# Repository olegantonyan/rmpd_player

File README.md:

rmpd_player

ESP32
VS1011
micro sd

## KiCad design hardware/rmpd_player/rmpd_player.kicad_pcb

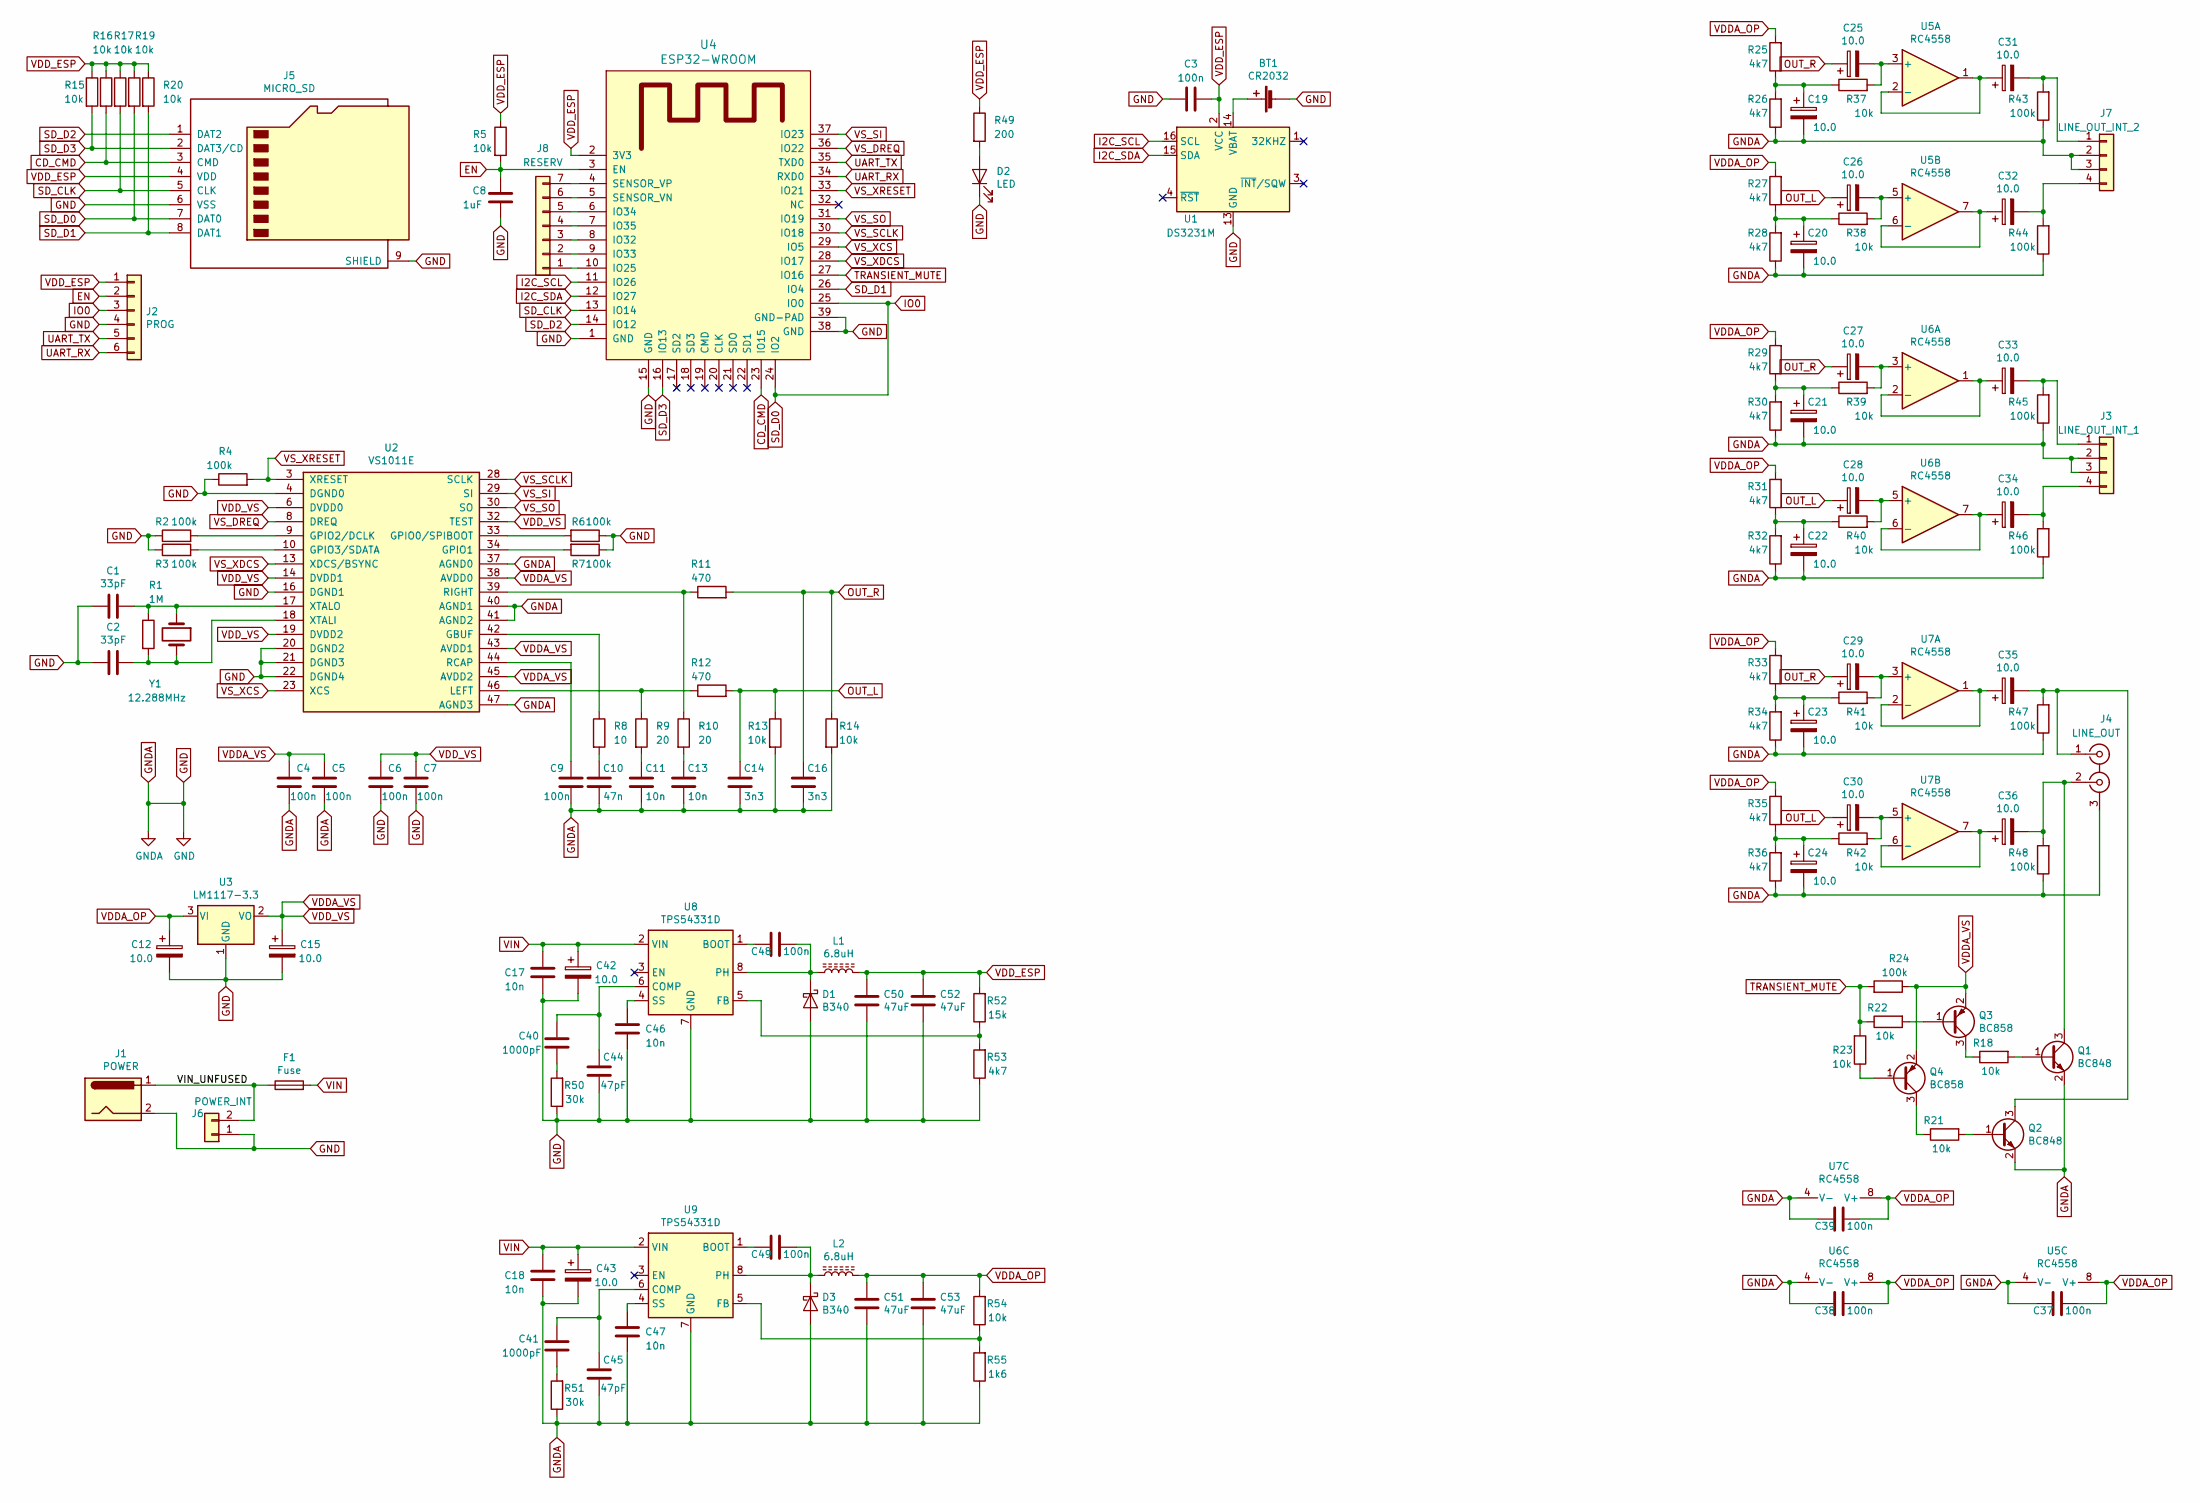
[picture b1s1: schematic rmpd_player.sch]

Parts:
BT1: CR2032; Keystone_103_1x20mm-CoinCell
C1, C2: 33pF; C_0805
C3, C4, C5, C6, C7, C9, C37, C38, C39, C48, C49: 100n; C_0805
C8: 1uF; C_0805
C10: 47n; C_0805
C11, C13, C17, C18, C46, C47: 10n; C_0805
C12, C15, C19, C20, C21, C22, C23, C24, C25, C26, C27, C28, C29, C30, C31, C32, C33, C34, C35, C36, C42, C43: 10.0; CP_Radial_D5.0mm_P2.50mm
C14, C16: 3n3; C_0805
C40, C41: 1000pF; C_0805
C44, C45: 47pF; C_0805
C50, C51, C52, C53: 47uF; C_1206
D1, D3: B340; PhotoDiode_SMD-DIL2_4.5x4
D2: LED; LED_D3.0mm
F1: Fuse; Fuse_SMD1206_Reflow
J1: POWER; BARREL_JACK
J2: PROG; Pin_Header_Straight_1x06_Pitch2.54mm
J3: LINE_OUT_INT_1; Pin_Header_Straight_1x04_Pitch2.54mm
J4: LINE_OUT; 2RCA
J5: MICRO_SD; Conn_uSDcard
J6: POWER_INT; Pin_Header_Straight_1x02_Pitch2.54mm
J7: LINE_OUT_INT_2; Pin_Header_Straight_1x04_Pitch2.54mm
J8: RESERV; Pin_Header_Straight_1x07_Pitch2.54mm
L1, L2: 6.8uH; L_6.3x6.3_H3
Q1, Q2: BC848; SOT-23
Q3, Q4: BC858; SOT-23
R1: 1M; R_0805
R2, R3, R4, R6, R7, R24, R43, R44, R45, R46, R47, R48: 100k; R_0805
R5, R13, R14, R15, R16, R17, R18, R19, R20, R21, R22, R23, R37, R38, R39, R40, R41, R42, R54: 10k; R_0805
R8: 10; R_0805
R9, R10: 20; R_0805
R11, R12: 470; R_0805
R25, R26, R27, R28, R29, R30, R31, R32, R33, R34, R35, R36, R53: 4k7; R_0805
R49: 200; R_0805
R50, R51: 30k; R_0805
R52: 15k; R_0805
R55: 1k6; R_0805
U1: DS3231M; SOIC-16W_7.5x10.3mm_Pitch1.27mm
U2: VS1011E; LQFP-48_7x7mm_Pitch0.5mm
U3: LM1117-3.3; SOT-223
U4: ESP32-WROOM
U5, U6, U7: RC4558; SO-8
U8, U9: TPS54331D; SOIC-8_3.9x4.9mm_Pitch1.27mm
Y1: 12.288MHz; Crystal_HC18-U_Vertical

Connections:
/VIN_UNFUSED: F1.1, J1.1, J6.2
CD_CMD: J5.3 (CMD), R16.2, U4.23 (IO15)
EN: C8.2, J2.2, R5.2, U4.3 (EN)
GND: BT1.2 (-), C1.2, C2.2, C3.1, C4.2, C5.2, C6.2, C7.2, C8.1, C9.2, C10.1, C11.1, C12.2, C13.1, C14.1, C15.2, C16.1, C17.2, C18.2, C19.2, C20.2, C21.2, C22.2, C23.2, C24.2, C37.2, C38.2, C39.2, C42.2, C43.2, C44.2, C45.2, C46.2, C47.2, C50.2, C51.2, C52.2, C53.2, D1.2 (A), D2.1 (K), D3.2 (A), J1.2, J2.4, J3.2, J3.3, J4.3 (EXT), J5.6 (VSS), J5.9 (SHIELD), J6.1, J7.2, J7.3, Q1.2 (E), Q2.2 (E), R2.1, R3.1, R4.1, R6.1, R7.1, R13.2, R14.2, R26.1, R28.1, R30.1, R32.1, R34.1, R36.1, R43.1, R44.1, R45.1, R46.1, R47.1, R48.1, R50.1, R51.1, R53.1, R55.1, U1.5 (GND), U1.6 (GND), U1.7 (GND), U1.8 (GND), U1.9 (GND), U1.10 (GND), U1.11 (GND), U1.12 (GND), U1.13 (GND), U2.4 (DGND0), U2.16 (DGND1), U2.20 (DGND2), U2.21 (DGND3), U2.22 (DGND4), U2.37 (AGND0), U2.40 (AGND1), U2.41 (AGND2), U2.47 (AGND3), U3.1 (GND), U4.1 (GND), U4.15 (GND), U4.38 (GND), U4.39 (GND-PAD), U5.4 (V-), U6.4 (V-), U7.4 (V-), U8.7 (GND), U9.7 (GND)
I2C_SCL: U1.16 (SCL), U4.11 (IO26)
I2C_SDA: U1.15 (SDA), U4.12 (IO27)
IO0: J2.3, J5.7 (DAT0), R19.2, U4.24 (IO2), U4.25 (IO0)
unnamed: BT1.1 (+), U1.14 (VBAT)
unnamed: C1.1, R1.1, U2.17 (XTALO), Y1.1
unnamed: C2.1, R1.2, U2.18 (XTALI), Y1.2
unnamed: C9.1, U2.44 (RCAP)
unnamed: C10.2, R8.2
unnamed: C11.2, R9.2
unnamed: C13.2, R10.2
unnamed: C19.1, R25.1, R26.2, R37.1
unnamed: C20.1, R27.1, R28.2, R38.1
unnamed: C21.1, R29.1, R30.2, R39.1
unnamed: C22.1, R31.1, R32.2, R40.1
unnamed: C23.1, R33.1, R34.2, R41.1
unnamed: C24.1, R35.1, R36.2, R42.1
unnamed: C25.2, R37.2, U5.3 (+)
unnamed: C26.2, R38.2, U5.5 (+)
unnamed: C27.2, R39.2, U6.3 (+)
unnamed: C28.2, R40.2, U6.5 (+)
unnamed: C29.2, R41.2, U7.3 (+)
unnamed: C30.2, R42.2, U7.5 (+)
unnamed: C31.1, U5.1, U5.2 (-)
unnamed: C31.2, J7.1, R43.2
unnamed: C32.1, U5.6 (-), U5.7
unnamed: C32.2, J7.4, R44.2
unnamed: C33.1, U6.1, U6.2 (-)
unnamed: C33.2, J3.1, R45.2
unnamed: C34.1, U6.6 (-), U6.7
unnamed: C34.2, J3.4, R46.2
unnamed: C35.1, U7.1, U7.2 (-)
unnamed: C35.2, J4.1 (IN1), Q2.3 (C), R47.2
unnamed: C36.1, U7.6 (-), U7.7
unnamed: C36.2, J4.2 (IN2), Q1.3 (C), R48.2
unnamed: C40.1, C44.1, U8.6 (COMP)
unnamed: C40.2, R50.2
unnamed: C41.1, C45.1, U9.6 (COMP)
unnamed: C41.2, R51.2
unnamed: C46.1, U8.4 (SS)
unnamed: C47.1, U9.4 (SS)
unnamed: C48.1, D1.1 (K), L1.1, U8.8 (PH)
unnamed: C48.2, U8.1 (BOOT)
unnamed: C49.1, D3.1 (K), L2.1, U9.8 (PH)
unnamed: C49.2, U9.1 (BOOT)
unnamed: D2.2 (A), R49.2
unnamed: J8.1, U4.10 (IO25)
unnamed: J8.2, U4.9 (IO33)
unnamed: J8.3, U4.8 (IO32)
unnamed: J8.4, U4.7 (IO35)
unnamed: J8.5, U4.6 (IO34)
unnamed: J8.6, U4.5 (SENSOR_VN)
unnamed: J8.7, U4.4 (SENSOR_VP)
unnamed: Q1.1 (B), R18.2
unnamed: Q2.1 (B), R21.2
unnamed: Q3.1 (B), R22.2
unnamed: Q3.3 (C), R18.1
unnamed: Q4.1 (B), R23.1
unnamed: Q4.3 (C), R21.1
unnamed: R2.2, U2.9 (GPIO2/DCLK)
unnamed: R3.2, U2.10 (GPIO3/SDATA)
unnamed: R6.2, U2.33 (GPIO0/SPIBOOT)
unnamed: R7.2, U2.34 (GPIO1)
unnamed: R8.1, U2.42 (GBUF)
unnamed: R10.1, R11.1, U2.39 (RIGHT)
unnamed: R9.1, R12.1, U2.46 (LEFT)
unnamed: R52.1, R53.2, U8.5 (FB)
unnamed: R54.1, R55.2, U9.5 (FB)
OUT_L: C14.2, C26.1, C28.1, C30.1, R12.2, R13.1
OUT_R: C16.2, C25.1, C27.1, C29.1, R11.2, R14.1
SD_CLK: J5.5 (CLK), R17.2, U4.13 (IO14)
SD_D1: J5.8 (DAT1), R20.2, U4.26 (IO4)
SD_D2: J5.1 (DAT2), U4.14 (IO12)
SD_D3: J5.2 (DAT3/CD), R15.2, U4.16 (IO13)
TRANSIENT_MUTE: R22.1, R23.2, R24.2, U4.27 (IO16)
UART_RX: J2.6, U4.34 (RXD0)
UART_TX: J2.5, U4.35 (TXD0)
VDDA_OP: C12.1, C37.1, C38.1, C39.1, C51.1, C53.1, L2.2, R25.2, R27.2, R29.2, R31.2, R33.2, R35.2, R54.2, U3.3 (VI), U5.8 (V+), U6.8 (V+), U7.8 (V+)
VDDA_VS: C4.1, C5.1, C6.1, C7.1, C15.1, Q3.2 (E), Q4.2 (E), R24.1, U2.6 (DVDD0), U2.14 (DVDD1), U2.19 (DVDD2), U2.32 (TEST), U2.38 (AVDD0), U2.43 (AVDD1), U2.45 (AVDD2), U3.2 (VO)
VDD_ESP: C3.2, C50.1, C52.1, J2.1, J5.4 (VDD), L1.2, R5.1, R15.1, R16.1, R17.1, R19.1, R20.1, R49.1, R52.2, U1.2 (VCC), U4.2 (3V3)
VIN: C17.1, C18.1, C42.1, C43.1, F1.2, U8.2 (VIN), U9.2 (VIN)
VS_DREQ: U2.8 (DREQ), U4.36 (IO22)
VS_SCLK: U2.28 (SCLK), U4.30 (IO18)
VS_SI: U2.29 (SI), U4.37 (IO23)
VS_SO: U2.30 (SO), U4.31 (IO19)
VS_XCS: U2.23 (XCS), U4.29 (IO5)
VS_XDCS: U2.13 (XDCS/BSYNC), U4.28 (IO17)
VS_XRESET: R4.2, U2.3 (XRESET), U4.33 (IO21)

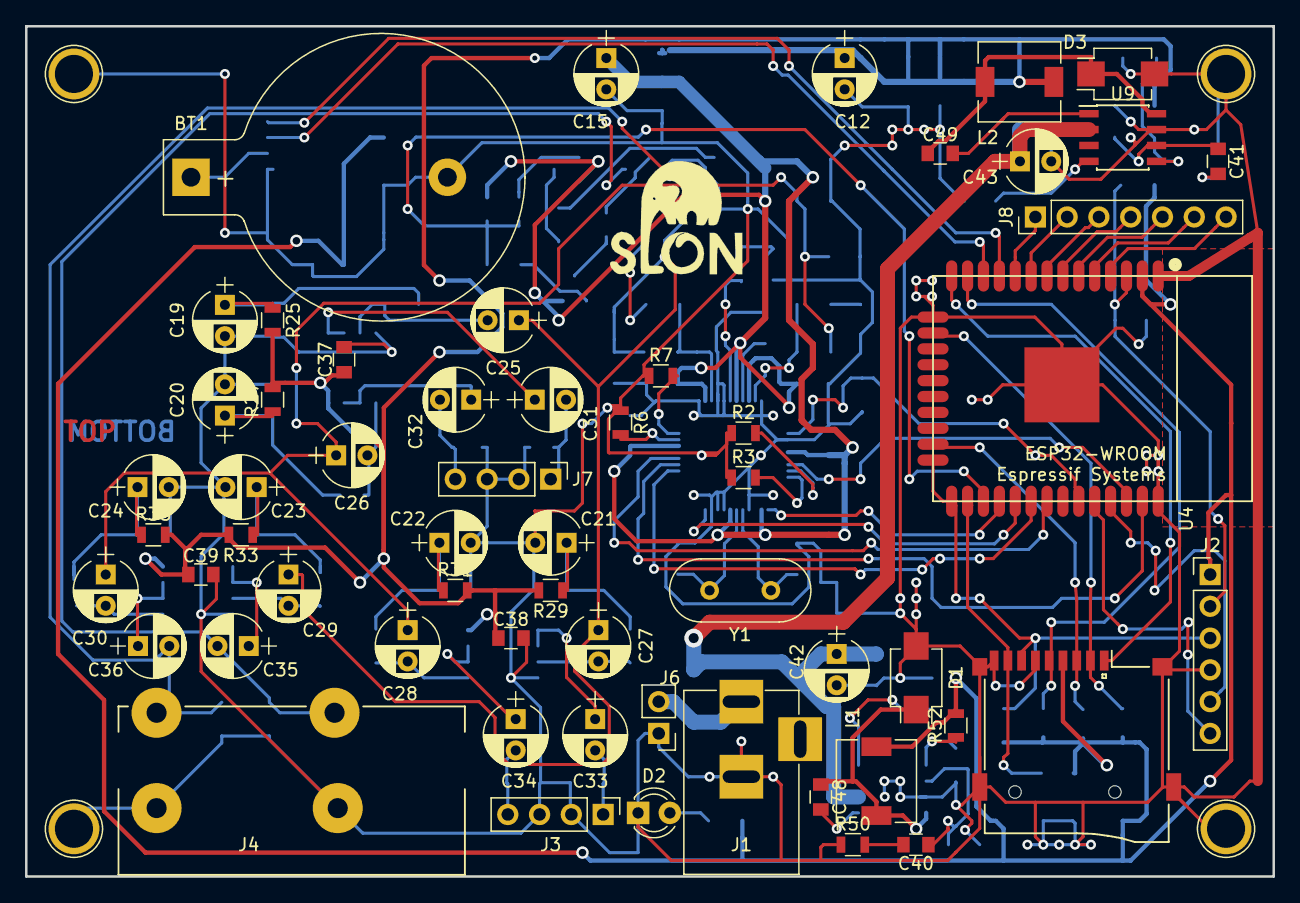
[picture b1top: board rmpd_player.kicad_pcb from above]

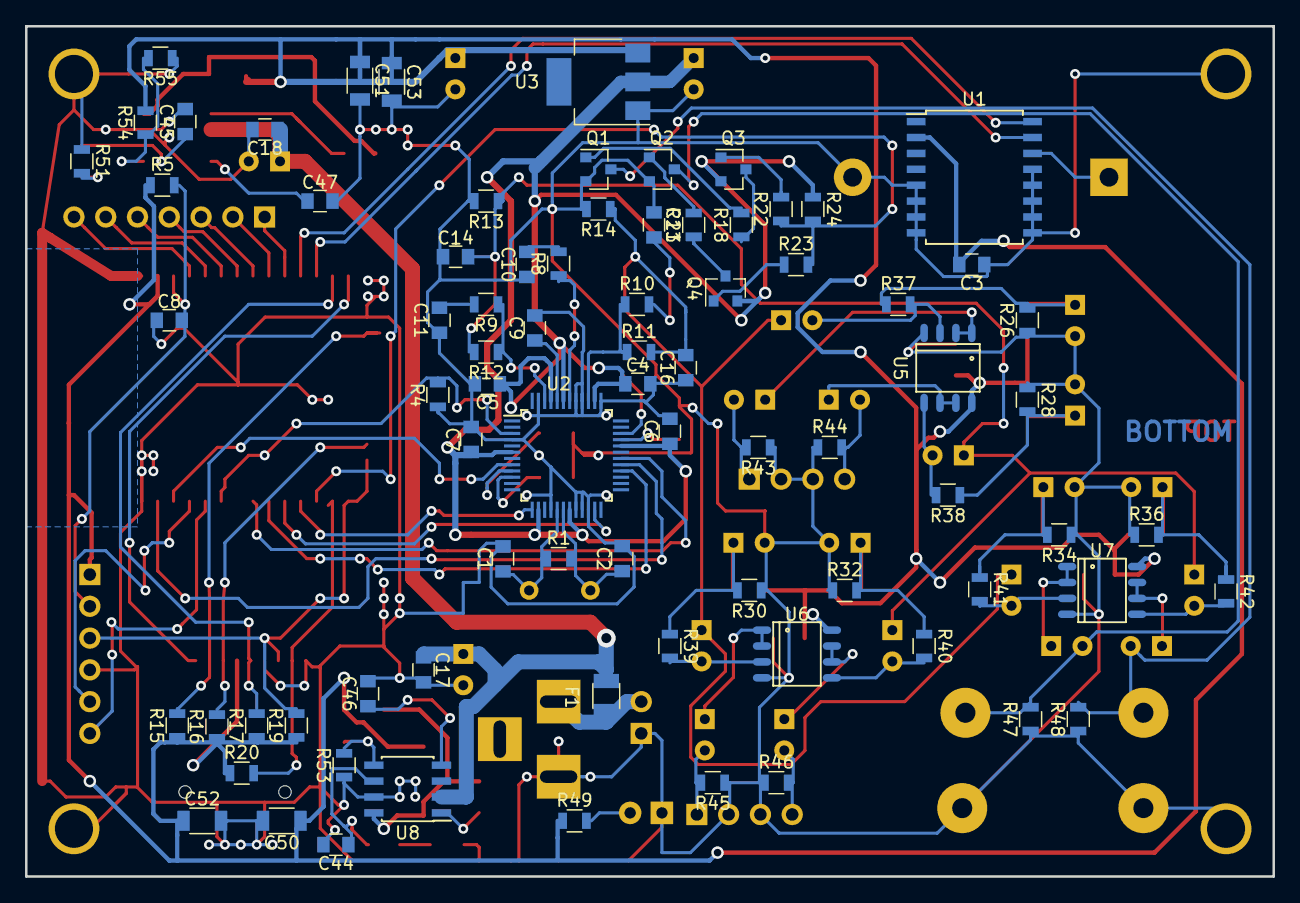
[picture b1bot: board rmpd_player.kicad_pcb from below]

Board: 2 copper layers, 99.7 x 67.9 mm, 137 parts (79 on the bottom side), 91 nets.

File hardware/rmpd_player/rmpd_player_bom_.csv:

Component,Description,Part,References,Value,Footprint,Quantity Per PCB,Datasheet
1,Single-cell battery,Battery_Cell,BT1,CR2032,Keystone_103_1x20mm-CoinCell,1,~
2,Polarized capacitor,CP,C12 C15 C19 C20 C21 C22 C23 C24 C25 C26 C27 C28 C29 C30 C31 C32 C33 C34 C35 C36 C42 C43,10.0,CP_Radial_D5.0mm_P2.50mm,22,~
3,Unpolarized capacitor,C,C40 C41,1000pF,C_0805_HandSoldering,2,~
4,Unpolarized capacitor,C,C3 C4 C5 C6 C7 C9 C37 C38 C39 C48 C49,100n,C_0805_HandSoldering,11,~
5,Unpolarized capacitor,C,C11 C13 C17 C18 C46 C47,10n,C_0805_HandSoldering,6,~
6,Unpolarized capacitor,C,C8,1uF,C_0805_HandSoldering,1,~
7,Unpolarized capacitor,C,C1 C2,33pF,C_0805_HandSoldering,2,~
8,Unpolarized capacitor,C,C14 C16,3n3,C_0805_HandSoldering,2,~
9,Unpolarized capacitor,C,C10,47n,C_0805_HandSoldering,1,~
10,Unpolarized capacitor,C,C44 C45,47pF,C_0805_HandSoldering,2,~
11,Unpolarized capacitor,C,C50 C51 C52 C53,47uF,C_1206_HandSoldering,4,~
12,"40V 3A Schottky Barrier Rectifier Diode, SMC",B340,D1 D3,B340,PhotoDiode_SMD-DIL2_4.5x4,2,http://www.jameco.com/Jameco/Products/ProdDS/1538777.pdf
13,Light emitting diode,LED,D2,LED,LED_D3.0mm,1,~
14,Fuse,Fuse,F1,Fuse,Fuse_SMD1206_HandSoldering,1,~
15,"double coaxial connector (BNC, SMA, SMB, SMC, Cinch/RCA, ...)",Conn_Coaxial_x2,J4,LINE_OUT,2RCA,1, ~
16,"Generic connector, single row, 01x04, script generated (kicad-library-utils/schlib/autogen/connector/)",Conn_01x04,J3 J7,LINE_OUT_INT_1,Pin_Header_Straight_1x04_Pitch2.54mm,2,~
17,,Micro_SD_Card-Connector,J5,MICRO_SD,Conn_uSDcard,1,http://katalog.we-online.de/em/datasheet/693072010801.pdf
18,DC Barrel Jack,Barrel_Jack,J1,POWER,BARREL_JACK,1,~
19,"Generic connector, single row, 01x02, script generated (kicad-library-utils/schlib/autogen/connector/)",Conn_01x02,J6,POWER_INT,Pin_Header_Straight_1x02_Pitch2.54mm,1,~
20,"Generic connector, single row, 01x06, script generated (kicad-library-utils/schlib/autogen/connector/)",Conn_01x06,J2,PROG,Pin_Header_Straight_1x06_Pitch2.54mm,1,~
21,"Generic connector, single row, 01x07, script generated (kicad-library-utils/schlib/autogen/connector/)",Conn_01x07,J8,RESERV,Pin_Header_Straight_1x07_Pitch2.54mm,1,~
22,Inductor with ferrite core,L_Core_Ferrite,L1 L2,6.8uH,L_6.3x6.3_H3,2,~
23,"0.1A Ic, 30V Vce, NPN Transistor, SOT-23",BC848,Q1 Q2,BC848,SOT-23,2,http://www.infineon.com/dgdl/Infineon-BC847SERIES_BC848SERIE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
24,"0.1A Ic, 30V Vce, PNP Transistor, SOT-23",BC858,Q3 Q4,BC858,SOT-23,2,http://www.fairchildsemi.com/ds/BC/BC856.pdf
25,Resistor,R,R8,10,R_0805_HandSoldering,1,~
26,Resistor,R,R2 R3 R4 R6 R7 R24 R43 R44 R45 R46 R47 R48,100k,R_0805_HandSoldering,12,~
27,Resistor,R,R5 R13 R14 R15 R16 R17 R18 R19 R20 R21 R22 R23 R37 R38 R39 R40 R41 R42 R54,10k,R_0805_HandSoldering,19,~
28,Resistor,R,R52,15k,R_0805_HandSoldering,1,~
29,Resistor,R,R1,1M,R_0805_HandSoldering,1,~
30,Resistor,R,R55,1k6,R_0805_HandSoldering,1,~
31,Resistor,R,R9 R10,20,R_0805_HandSoldering,2,~
32,Resistor,R,R49,200,R_0805_HandSoldering,1,~
33,Resistor,R,R50 R51,30k,R_0805_HandSoldering,2,~
34,Resistor,R,R11 R12,470,R_0805_HandSoldering,2,~
35,Resistor,R,R25 R26 R27 R28 R29 R30 R31 R32 R33 R34 R35 R36 R53,4k7,R_0805_HandSoldering,13,~
36,Extremely Accurate I2C-Integrated RTC/TCXO/Crystal SOIC-16,DS3231M,U1,DS3231M,SOIC-16W_7.5x10.3mm_Pitch1.27mm,1,http://datasheets.maximintegrated.com/en/ds/DS3231.pdf
37,,ESP32-WROOM,U4,ESP32-WROOM,ESP32-WROOM,1,
38,"800mA Low-Dropout Linear Regulator, 3.3V fixed output, TO-220/TO-252/TO-263/SOT-223",LM1117-3.3,U3,LM1117-3.3,SOT-223,1,http://www.ti.com/lit/ds/symlink/lm1117.pdf
39,"Dual General Purpose, Operational Amplifier, DIP-8/SOIC-8/SSOP-8",RC4558,U5 U6 U7,RC4558,SO-8,3,http://www.ti.com/lit/ds/symlink/rc4558.pdf
40,"2A, Step Down DC-DC Converter with Eco-mode, 3.5-28V Input Voltage, SO-8",TPS54233,U8 U9,TPS54331D,SOIC-8_3.9x4.9mm_Pitch1.27mm,2,http://www.ti.com/lit/ds/symlink/tps54233.pdf
41,VLSI VS1011E,VS1011E,U2,VS1011E,LQFP-48_7x7mm_Pitch0.5mm,1,/home/oleg/projects/rmpd_player/doc/vlsi/vs1011.pdf
42,Two pin crystal,Crystal,Y1,12.288MHz,Crystal_HC18-U_Vertical,1,~





Component Groups:,42
Component Count:,137
Fitted Components:,137
Number of PCBs:,1
Total components:,137
Schematic Version:,
Schematic Date:,2018-12-25
BoM Date:,Thu 06 Jun 2019 21:27:45 EET
Schematic Source:,/home/oleg/projects/rmpd_player/hardware/rmpd_player/rmpd_player.sch
KiCad Version:,Eeschema 5.1.2-5.1.2

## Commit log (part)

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2018-11-03 optimizations
2018-11-04 newline
2018-11-04 naked freertos
2018-11-04 naked freertos 10 working
2018-11-04 naked freertos 10 working with cubemx
2018-11-04 naked freertos 10 working with cubemx cleanup
2018-11-04 uart receive
2018-11-04 cli cleanup
2018-11-04 cli dymanic memory
2018-11-04 cli static memory
2018-11-04 leds
2018-11-04 leds app trim stack size
2018-11-04 leds app fix blinks off
2018-11-04 thread names
2018-11-04 trim stack size
2018-11-04 runtime stats
2018-11-05 docs added
2018-11-05 freertos source tarball
2018-11-07 added nodemcu
2018-11-08 app.lua playing with uart
2018-11-10 playing with tmr in lua
2018-11-11 no save wifi config
2018-11-14 ntp multiple servers
2018-11-14 remove network.lua
2018-11-14 no ntp autosync
2018-11-16 lua read/write files example
2018-11-17 web server index.html file
2018-11-17 web server extract
2018-11-17 web server css/ico static serve
2018-11-17 use raw espressif sdk
2018-11-17 rtos sdk espressif
2018-11-17 tweek config
2018-11-18 dhcp server config
2018-11-18 project subdirs
2018-11-18 ntp with thread
2018-11-18 wifi subdir
2018-11-18 no debug output
2018-11-19 idf repo
2018-11-19 idf rename
2018-11-19 esp32 idf path
2018-11-19 wifi not working yet
2018-11-19 checkpoint
2018-11-19 wifi working - storage ram
2018-11-19 prettify
2018-11-19 idf master
2018-11-19 http server
2018-11-20 160mhz; vlsi docs
2018-11-20 docs
2018-11-20 spiffs with file
2018-11-20 flash_all target
2018-11-20 flash_all target build mkspiffs comment
2018-11-21 spiffs prettify; http serves files from spiffs
2018-11-21 config
2018-11-21 webapp added
2018-11-21 webapp enable --experimental-scope-hoisting
2018-11-21 milligram from npm
2018-11-21 idf update
2018-11-22 webapp purecss
2018-11-23 webpack to build webapp
2018-11-23 no href on a tags
2018-11-23 settings form stub
2018-11-24 webapp fetch settings proto
2018-11-24 web server respond with json
2018-11-24 cleanup dependencies
2018-11-24 fewer deps
2018-11-24 webapp save wifi settings
2018-11-25 save-fetch cleanup webapp
2018-11-26 save wifi config and reconnect
2018-11-27 config module; refactor
2018-11-28 webapp state saving disable button; no debug output
2018-11-28 micro sd
2018-11-29 sd card light cleanup
2018-11-29 readdir
2018-11-30 more schematic; vs1011 library
2018-11-30 more schematic
2018-12-01 100k pull-downs on gpio vlsi
2018-12-01 spi connection vlsi schematic
2018-12-01 vdd - vdda connction
2018-12-02 spi stub
2018-12-02 spi command r/w works
2018-12-02 vs1011 spi refactor
2018-12-02 vs1011 spi refactor 2
2018-12-02 checkpoint/ no luck with vs1011 audio playback
2018-12-03 player start/stop with queues
2018-12-03 vs1011 mute circuit
2018-12-03 vs1011 automute
2018-12-03 lm1117 schematic
2018-12-04 fix log
2018-12-04 scheduler added
2018-12-04 add now_playing filename
2018-12-04 fix null now_playing filename
2018-12-04 spread task priorities
2018-12-05 percent_pos added
2018-12-05 ds3231 stubs added
2018-12-05 ds3231 read time
2018-12-05 ds3231 read time fix
2018-12-06 rtc time
2018-12-06 i2c mutex
2018-12-06 ds3231 generate start condition
2018-12-08 2rca footprints
2018-12-09 power_int pinheader
2018-12-10 no more CMakeLists.txt
2018-12-10 tht diode
2018-12-11 minor cleanup
2018-12-15 schematic op amp buffer; bom list
2018-12-15 op amps caps
2018-12-15 player task high priority; larger file buffer
2018-12-15 1000Hz tick rate
2018-12-16 moar pcb
2018-12-16 power led
2018-12-16 smaller pcb
2018-12-17 bom list update
2018-12-18 kicad library sources added
2018-12-18 wifi disconnect possible fix
2018-12-20 clock init before wifi
2018-12-21 fix wifi disconnects - sntp issue
2018-12-21 player volume
2018-12-21 2MBaud serial fkash
2018-12-22 vs1011 optimize with dreq interrupt
2018-12-22 extrat util/ submodule
2018-12-22 better vdd route to ds3231
2018-12-23 percen pos slider
2018-12-23 webapp images
2018-12-23 webapp cleanup empty state
2018-12-24 wip: volume control
2018-12-26 new pcb
2018-12-26 fix set volume
2018-12-26 malloc filename size fix
2018-12-26 saving volume setting to nvs
2018-12-26 bass control vs1011
2018-12-27 tone controls implemented
2018-12-28 webapp prettify
2018-12-28 stubs for next/prev playback control
2018-12-28 update status on volume update
2018-12-28 connection: close always
2018-12-29 resursive subfolders
2018-12-29 scheduler next
2018-12-29 scheduler wait for stopped on next
2018-12-29 scheduler no wait for stopped on next
2018-12-29 scheduler count number of medifiles with callback
2018-12-30 scheduler prev/next
2018-12-30 refactor scheduler prev/next
2018-12-30 refactor scheduler random - stub with web
2018-12-31 refactor scheduler random - get state from the scheduler itself
2018-12-31 stub for rng
2018-12-31 random implemented
2019-01-01 refactor vs1011 driver to use abstract read_func
2019-01-02 stream stub
2019-01-02 sd max 15 open files
2019-01-02 system/reboot implemented
2019-01-02 system show free heap adn mac
2019-01-02 show ip addr on system page
2019-01-03 show reset reason on system page
2019-01-03 show chip revision on system page
2019-01-03 uptime on system page
2019-01-04 stream works, kind of. hardcoded
2019-01-04 MSG_WAITALL on socket in stream_read
2019-01-04 extract VS1011_BUFFER_SIZE macro
2019-01-05 stream with ring buffer
2019-01-05 stream chunk buffer optimal size
2019-01-05 parse url implemented
2019-01-05 minor refactoring
2019-01-05 extract url_parse
2019-01-06 support pls format and bullshit-with-link format fro streaming playlists
2019-01-06 stream buffer increase
2019-01-06 extact stream_playlist
2019-01-06 stubs for web auth
2019-01-07 basic auth implemented
2019-01-07 softap from config; reconnect hacks
2019-01-08 webapp show decode time
2019-01-08 remove depricated comment
2019-01-09 fix possible buffer overflow in stream http header
2019-01-09 static ap iface ip on system page
2019-01-09 system page refresh button; confirm reboot
2019-01-09 fix typo in password label
2019-01-10 timezone support
2019-01-10 change partitions layout - 256k for spiffs; vendor posix_tz_db into the project
2019-01-12 task list & runtime stats on system page
2019-01-12 webapp state cleanup
2019-01-12 webapp and mkspiffs make targets
2019-01-13 play around with memory usage
2019-01-13 enable stack smash protection
2019-01-16 fix uri matching
2019-01-16 add reason to disconnected event
2019-01-16 wifi improvements
2019-01-17 stream start wait for buffer half-full
2019-01-18 mdns added. not sure how test it though
2019-01-19 remove unnecessory code
2019-01-20 task list / stack free rename
2019-01-20 extract recurse module
2019-01-20 remove redundant code
2019-01-20 move random into playlist module
2019-01-22 stream retries
2019-01-28 prepare stream scheduler
2019-01-28 prepare stream scheduler; fix clock set timezone error
2019-01-29 scheduler wait for wifi if there is a stream
2019-01-29 equlize some capacitors values
2019-01-31 stubs for priopity streams
2019-02-02 stream scheduler implemented
2019-02-02 stream scheduler optimize with error callback
2019-02-02 stream scheduler moar probe timeout wehn any alive streams present
2019-02-03 stream scheduler lower priority
2019-02-03 disable mdns
2019-02-03 embed letsencrypt root certs
2019-02-03 embed zones.json
2019-02-04 lower baudrate for flasher
2019-02-06 hide passwords from logs
2019-02-06 syubs for remote gateway
2019-02-08 no more http util: need a better approach to this shit
2019-02-13 http to server kind of works
2019-02-14 http read works with events
2019-02-15 extract now_playing command
2019-02-16 implemented remote control architecture
2019-02-16 track_begin & track_end
2019-02-17 incoming commands arch
2019-02-17 pdjson component; dump big incomming data to sd
2019-02-18 stream json parse for incomming commands
2019-02-19 fix stream json parsing
2019-02-20 player thread increase stack
2019-02-22 timezones pdjson stream parsing
2019-02-23 update_setting command to set timezone
2019-02-24 show version info on system page; extract user-agent to util/sysinfo
2019-02-24 set russian oem code page for fatfs
2019-02-25 update partitions; move chip revision to useragent
2019-02-25 webapp: npm audit fix; remove tests
2019-02-25 remote gate increase stack
2019-02-25 cleanup tempfiles on start implemented tempfile_init
2019-02-26 move sysinfo to a new namespace; stubs for firmware update
2019-02-27 update usera agent
2019-02-28 online/offline status show in web ui; show cloud addr on system page
2019-02-28 change cloud icon in webapp
2019-03-01 update_software incoming command
2019-03-03 https ota implemented via update_software command
2019-03-03 fw update rollback support
2019-03-03 thread names == TAGs
2019-03-03 move scheduler to playlist/offline
2019-03-03 stream wait longer for half-full buffer
2019-03-03 esp-idf update
2019-03-04 change user-agent a bit
2019-03-19 option to disable certs verification
2019-03-19 wider menu
2019-03-19 enable certs after each fw update
2019-03-19 file_download
2019-03-21 skip authorization web when came from AP interface
2019-03-22 improve now playing
2019-03-23 config_ap_pass
2019-03-23 default config header; fix power_on command after track_begin
2019-03-23 change reset capacitor to 1uF
2019-03-24 implement own https ota
2019-04-02 on fw update notify new version
2019-04-09 files download WIP
2019-04-09 files download optimize WIP
2019-04-10 files download optimize WIP 240mhz
2019-04-10 files download optimize async file write
2019-04-12 fix playlist saving json
2019-04-13 closed to cloud scheduler
2019-04-13 update playlist outgoing
2019-04-18 trying to update sntp
2019-04-24 working sntp
2019-04-24 bump to 0.0.6 version
2019-04-25 kicad update
2019-05-09 ip addr in all outgoing commands
2019-05-17 delete_all_file command stub
2019-05-17 delete_all_file command implemented
2019-05-17 stop offline scheduler before delete_all_file
2019-05-18 removing non-paylist files upon finishing download
2019-05-18 cloud scheduler implemented
2019-05-18 cloud scheduler fix next button error
2019-05-18 offline random decrease trait
2019-05-18 download infinite retires
2019-05-19 memory optimizations
2019-05-20 cleanup in thread
2019-05-21 cleanup delay on start; 0 allocation unit size
2019-05-21 read ahead created; no luck so far
2019-05-22 use read/write calls
2019-05-22 buffered fwrite in http/files_download
2019-05-22 less stack
2019-05-22 esp_http_client separate tx buffer size in config
2019-05-23 fix buf
2019-05-23 update idf
2019-05-24 increase http timeounts
2019-05-25 stopping files download
2019-05-25 fix firmware update
2019-05-25 webapp timeouts optimize
2019-05-25 fw update stops cleanup and donload
2019-05-25 show syncronizing loader in webapp
2019-05-25 setvbuf in cleanup_files
2019-05-25 smaller stack buffers in http
2019-05-25 tweaking mbedtls
2019-05-26 tweaking mbedtls out buffer size; more codec memory
2019-05-26 skip notify existing files
2019-05-26 npm audit fix
2019-05-26 fix bug multiple start-stops (close #2)
2019-05-27 improve offline scheduler deinit
2019-05-28 use parceljs to build webapp
2019-05-28 use parceljs to build webapp - no sourcemaps
2019-05-28 webapp update .node-version
2019-05-29 minor fixes
2019-05-30 small memory optimizations
2019-05-30 wifi 4 static buffers
2019-05-30 wear level 4k sector
2019-06-06 kicad bom list update
2019-06-08 version bump - 1.0.0 first stable realease
2019-06-28 add cloudflare ntp server
2019-07-01 webapp npm update
2019-07-03 pfjson_helper - a new way to implement parser state machine
2019-07-05 add type to track
2019-07-05 datetime util added
2019-07-06 prepare to traverse schedule_intervals
2019-07-07 traverse advertising tracks
2019-07-08 track copy
2019-07-09 advertising seems to work
2019-07-10 improve advertising
2019-07-11 small improvemnts in advertiring sched
2019-07-13 webapp: npm update; npm audit fix
2019-07-17 update footprints to reflow
